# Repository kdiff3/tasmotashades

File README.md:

# tasmotashades

This is an integrated PCB for automating shades with one Nema 17 stepper motor.
I used the original Nema mounting brackets and some stock roller shades.

The controller is based on a nodeMCU and it is designed to work with Tasmota.
Therefore, it is wifi enabled and can be integrated in several different home automation server systems (e.g., by using MQTT).
Further reading for configuring Tasmota can be found here:
https://tasmota.github.io/docs/Blinds-and-Shutters/#using-stepper-motors

Please use Kicad https://www.kicad.org/ for viewing and exporting the PCB schematics.

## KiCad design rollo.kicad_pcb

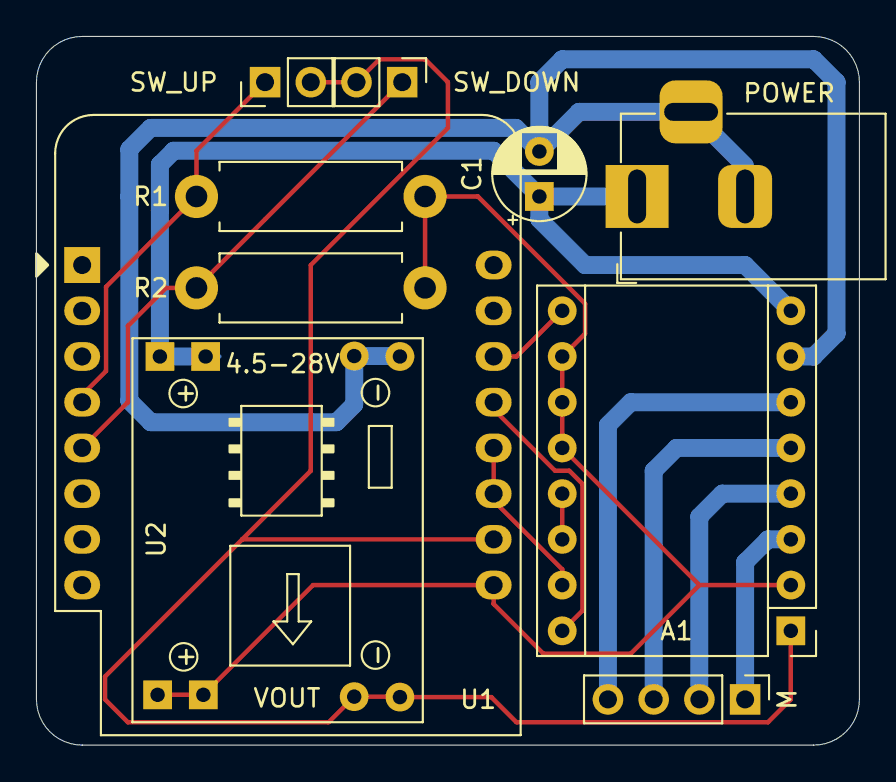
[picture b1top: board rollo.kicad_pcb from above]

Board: 2 copper layers, 45.7 x 39.4 mm, 10 parts (0 on the bottom side), 14 nets.

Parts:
A1: Pololu_Breakout_A4988; Pololu_Breakout-16_15.2x20.3mm
C1: CP; CP_Radial_D5.0mm_P2.50mm
M: Conn_01x04; PinHeader_1x04_P2.54mm_Vertical
POWER: Barrel_Jack; BarrelJack_Horizontal
R1, R2: 4.7k; R_Axial_DIN0411_L9.9mm_D3.6mm_P12.70mm_Horizontal
SW_DOWN: SW_Push; PinHeader_1x02_P2.54mm_Vertical
SW_UP: SW_Push; PinHeader_1x02_P2.54mm_Vertical
U1: WeMos_D1_mini; WEMOS_D1_mini_light
U2: MP1584EN; SRT_MPT1584EN_Module

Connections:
+12V: A1.8, C1.1, POWER.1, U2.1
GND: A1.7, C1.2, POWER.2, POWER.3, U2.2
unnamed: A1.1, SW_DOWN.2, SW_UP.2, U1.10, U2.4
unnamed: A1.3, M.1
unnamed: A1.4, M.2
unnamed: A1.5, M.3
unnamed: A1.6, M.4
unnamed: A1.9, U1.14
unnamed: A1.2, A1.10, A1.11, A1.12, R1.1, R2.1, U1.9, U2.3
unnamed: A1.13, A1.14
unnamed: A1.15, U1.11, U1.12
unnamed: A1.16, U1.13
unnamed: R1.2, SW_UP.1, U1.4
unnamed: R2.2, SW_DOWN.1, U1.5

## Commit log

2022-05-05 Added the entire Kicad project
